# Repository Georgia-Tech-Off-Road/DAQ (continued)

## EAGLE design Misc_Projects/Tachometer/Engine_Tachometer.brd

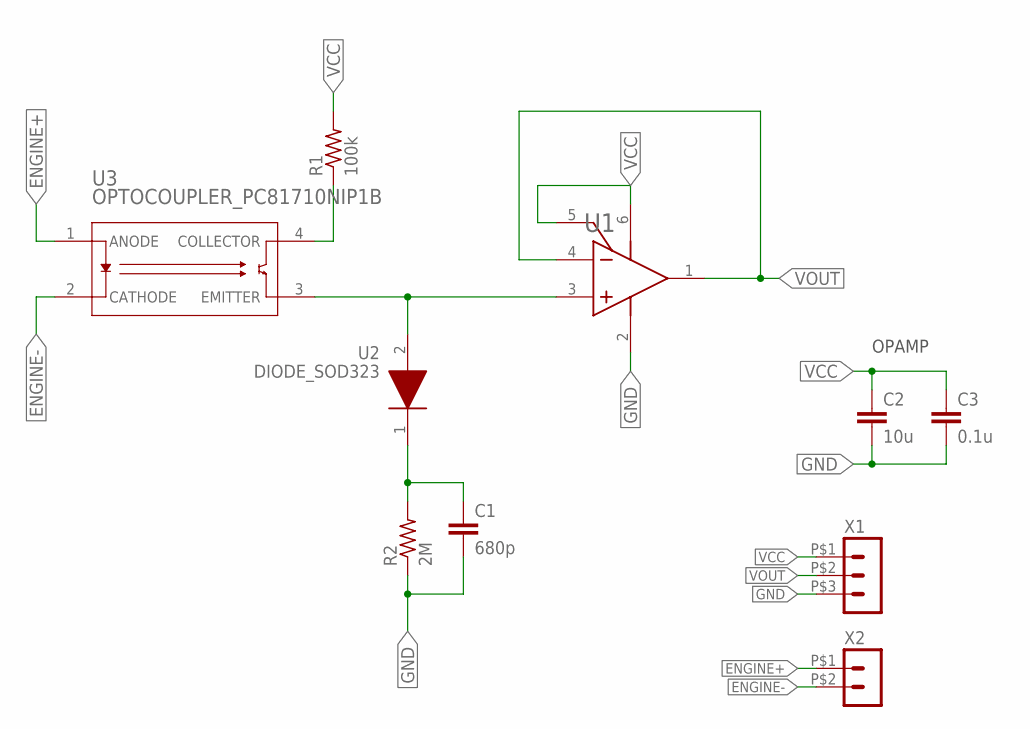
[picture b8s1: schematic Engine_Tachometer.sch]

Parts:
C1: 680p; C0603
C2: 10u; C1206
C3: 0.1u; C0603
R1: 100k; R1206
R2: 2M; R0603
U1: OPAMP_LMH6611MKE; MK06A
U2: DIODE_SOD323; SOD-323_1P8X1P35_ONS
U3: OPTOCOUPLER_PC81710NIP1B; SOP_PC8171_SCT
X1: HEADER_POS3_43650-0300; 43650-0300
X2: HEADER_POS2_43650-0200; 43650-0200

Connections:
ENGINE+: U3.1 (ANODE), X2.P$1 (1)
ENGINE-: U3.2 (CATHODE), X2.P$2 (2)
GND: C1.2, C2.2, C3.2, R2.1, U1.2 (V-), X1.P$3 (3)
unnamed: R1.1, U3.4 (COLLECTOR)
unnamed: U1.3 (IN+), U2.2, U3.3 (EMITTER)
unnamed: C1.1, R2.2, U2.1
VCC: C2.1, C3.1, R1.2, U1.5 (~DIS), U1.6 (V+), X1.P$1 (1)
VOUT: U1.1 (OUT), U1.4 (IN-), X1.P$2 (2)

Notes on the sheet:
OPAMP

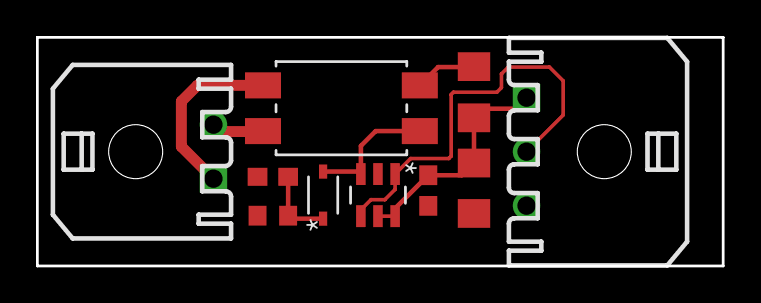
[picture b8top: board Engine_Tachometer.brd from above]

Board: 2 copper layers, 38.1 x 12.7 mm, 10 parts (0 on the bottom side), 8 nets.

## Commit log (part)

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2020-12-27 Testing if I can push to remote
2020-12-31 IMU330DHCX Final Code
2020-12-31 IMU330DHCX Header Upload
2021-01-03 Added the HE sensor case for Rev2
2021-01-14 Add ISM330DHCX Library
2021-01-15 Conceptual Brainstorming Changes
2021-01-15 Added diff library for eagle
2021-01-15 Added relevant mailing lists for recruitment emails.
2021-01-15 Updated .gitignore and cleaned up Eagle autosaves
2021-01-15 Removed Eagle Libraries
2021-01-16 Created HESensorRev3 case and added documentation
2021-01-16 Added STL Files for Printing
2021-01-16 Created file for IMU
2021-01-16 Increase ranges for accel, gyro, and data rates
2021-01-16 Documentation changes
2021-01-17 Eagle files for PCB
2021-01-18 Added schematic and board files
2021-01-20 Updated Eagle board and software
    Added female headers, routed HE inputs
    Added theoretical diff controller code basis
2021-01-23 Made minor edits to documentation
2021-01-23 Added step in eagle libraries guide
2021-01-27 Test example
2021-01-31 Added small functions to utility
2021-01-31 Changed Lib .readme
2021-01-31 Added automatic Arduino library symlinks generator
2021-02-01 Resized speed sensor case for larger shaft
2021-02-03 Fixed parts so that they can actually be assembled.
2021-02-05 Added STL Files for IMU Case Printing
2021-02-09 Renamed folder from "new_project" to "Dyno Board"
2021-02-10 Renamed folder and added Load Cell Manual.
2021-02-13 Fixed data being deleted after stopped collecting bug
2021-02-13 Added changes that I do not remember
2021-02-18 Created documentation for the engine dyno
2021-02-19 Added documentation for engine dyno
2021-02-19 Added lots of changes for first working prototype
2021-02-24 replaced old motor driver; added local libraries
2021-02-24 Minor bug fixes
2021-02-28 pcb from 02-28
2021-03-04 edited h-bridge
2021-03-04 Minor changes on PCB, ready for manufacturing
2021-03-07 Began work on UARTComms class and Sensor class
2021-03-07 small changes to Sensor
2021-03-07 added changes to update function
2021-03-07 Adding __init__ for EngineDyno Layout
2021-03-10 Pseudocoded rest of Comms functions to be written
2021-03-12 Reconstructed FreqMeasureMulti without using FreqMeasureMulti library
2021-03-12 Moved IMU Lib folder code to Libraries folder
2021-03-12 Moved Dyno code in Lib folder to Libraries folder
2021-03-16 Added functionality for zero rpm
2021-03-17 Finished Aux Daq Case
2021-03-19 Seven Segment Code done
2021-03-20 added matlab file for theoretical speed sensor calculations
2021-03-21 Added update for serial input
2021-03-21 Auto stash before merge of "differential_controller" and "origin/differential_controller"
2021-03-21 Fixed compilation errors and implemented switch/serial control mode
2021-03-24 Finished theoretical implementation using FreqMeasureMulti
2021-03-25 Adding data parser for recording and graphing data collected from sensors
2021-03-26 Adding the data parser to change bin data files in to usable data to graph and add to an excel sheet
2021-03-26 Reversed motor pins to work with new differential
2021-03-26 Working UARTComms and SDWrite libraries. Next step is extending Sensor functionality.
2021-03-26 temporary commit
2021-03-26 Tidying the parser and preparing for plotting
2021-03-26 Sensor updates, LDS example
2021-03-27 Fixed some problems with LDS example, Sensor id bug still exists---id needs to be 1 byte for now
2021-03-27 aux daq unit code with two sensors
2021-03-27 Quick fix for diff controller breaking when moving to state 1 and state2
2021-03-27 Added more sensor libraries
2021-03-27 Give to Akash code
2021-03-28 Changes from grind day
2021-03-30 Beginning data parser optimizations
2021-04-01 Need to change branches
2021-04-01 Small changes to DataCollection
2021-04-02 Adding more cleanup to parser
2021-04-02 Added functions to implement for data import
2021-04-02 Added Sensor ID's to Daata
2021-04-04 Before merge with aux_daq_util
2021-04-04 Adding most Import functionality and updating Data and SensorId accordingly
2021-04-04 Added Pinout image and modified Dyno_test to follow pinout
2021-04-06 Renamed Folder to Engine_Dyno
2021-04-06 Updated HEtest.ino to work with new HE Sensor library
2021-04-06 Added psedu-code/code for speed sensor?
    Please double-check
2021-04-07 Finished minimum worked version of SpeedSensor
2021-04-07 Added SpeedSensor to Sensor.h
2021-04-07 Cleaning up parser, adding csv file for data, and beginning update to Sensor objects and ID's
2021-04-07 Updating Sensor ID numbers
2021-04-07 hotfix
2021-04-07 Code ready for dyno test
2021-04-09 Added SerialTest.ino
2021-04-09 Git witchcraft merge
2021-04-10 Comments added
2021-04-11 Code uploaded for the 4/11/2021 test day
    Syntax errors fixed
2021-04-13 Code uploaded for test day 4/11/21
2021-04-17 Fixed errors with Sensor Class
2021-04-17 Adding data parsers
2021-04-17 Updated SensorId
2021-04-17 Changes to mock wireless testing
2021-04-17 Manual merge of dashboard into master
2021-04-21 Adding syntax fixes in import
2021-04-21 Changing serial port to None to get it working
2021-04-23 On the verge of glory
2021-04-25 pls no conflict
2021-04-28 Made better averaging algorithm for speed sensor
2021-05-01 Updated Dashboard Code (non-working)
2021-05-01 Display diff position on dashboard
2021-05-01 Added StateSensor and diff_state functionality for writing diff_state to h_seg on dash
2021-05-12 Updated documentation template
2021-06-02 DashHub code changes from Arizona
2021-06-18 Removed Documentation
2021-06-18 Removed Resources Folder
2021-06-26 Removed HallEffectSpeedSensor
2021-06-29 Removed Libraries
2021-07-08 Updates to First Dyno test
2021-08-21 Added ability to zero load cell
2021-09-03 Created new branch and folder for new 2022 aux_daq
2021-09-06 Added rough draft of shockdyno arduino code
2021-09-12 Added optional headers for strain gauge breakout
2021-09-12 added project for shock dyno
2021-09-19 Working on board files
2021-09-19 Minor DRC fixes and trace thickening
2021-09-19 Minor silkscreen changes
2021-09-19 completed shock dyno PCB schematic
2021-09-20 Boards designs before 9/19 design review
2021-09-22 Moved phat connector
2021-09-24 shock dyno PCB updates
2021-09-26 Just a bit of work I did on Tuesday
2021-09-26 Added kill motor scenario and fixed scale for motor_control
2021-09-26 added name to shock dyno PCB
2021-09-27 More work done to dash hub and dial, gps board added
2021-09-27 Adding design draft of comms testing board
2021-09-28 Finished everything except silkscreen
2021-09-29 final touches to shock dyno PCB
2021-09-29 Adding finished comms testing board
2021-09-29 Updated silkscreen
2021-09-29 final touches to shock dyno PCB part 3
2021-10-01 Linear Regulator
2021-10-06 Added wireless receiver PCB
2021-10-08 Added new linear regulator and XBee silkscreen to dashhub
2021-10-10 Added gps to dashhub
2021-10-15 Added OLED
2021-10-17 Added missing capacitor values
2021-10-17 Moving stuff around on the dashhub #pain
2021-10-19 Changed names on dashboard to reflect pins
2021-10-20 Changed regulator placement
2021-10-22 Fixed the dashhub #everything
2021-10-27 Added resistor values to dashhub and board
2021-10-31 Fixed IMU test code
2021-11-04 IMU Code works with aux_daq
2021-11-05 OLED code added
2021-11-05 Added OLED code
2021-11-05 Added Aux Daq Code and wireless comms throughput
2021-11-12 Test day AuxDaq code
2021-12-07 Added Testing Day Nov 20 Code
    It doesn't work
2021-12-07 Finished routing aux daq
2021-12-13 Started making Aux Daq V2 Case
2021-12-29 Did Aux Daq Design Review
2022-01-14 oriented load cell connector correctly
2022-01-14 added labels to silkscreen on shock dyno PCB
2022-01-14 Edited Dashboard code
2022-01-19 Updated Aux Daq PCB to include LED and button outputs
2022-01-21 Added aux daq definitions file
2022-01-24 Finished shock dyno updates
2022-02-02 Removed incorrect IMU case
2022-02-06 Updated all dashboard stuff
2022-02-11 Dashboard Code Organization
2022-02-13 modified Shock_Dyno.ino for ads8688
2022-02-20 fixed Shock Dyno disable
2022-02-28 removed relay from shock dyno
2022-03-02 Removed bad dashboard code
2022-03-04 changed strain gauge board connectors to microfit
2022-03-04 Added new Light Gate boards
2022-03-06 Light Gate Updates
2022-03-06 Fixeed light gate start board
2022-03-07 Created second aux daq digital breakout
2022-03-09 Coded light gates
2022-03-13 Attached GPS block for dashboard
2022-04-01 Updated Wireless Receiver Code
2022-04-03 Updated DynoTest Code
2022-04-07 COde from testing day
2022-04-10 Updated aux daq case design and added demo code for end of year review
2022-04-24 added power trace to shock dyno board ADC
2022-04-24 added more clearance for standoff pins on shock dyno
2022-04-24 edit dashboard code
2022-05-06 Wrote CVTStiffness testing code
2022-05-06 FIXED DASHBOARD LETS GOOO
2022-06-02 Dashboard code from Tennessee
2022-08-25 Engine dyno speed sensor updates
2022-09-13 new pcb files
2022-09-28 Updated to 7mil trace instead of 5mil
2022-10-02 Working on dashboard code
2022-10-09 CODE
2022-10-30 Updated pull ups on dashboard
2022-11-03 Wireless Communications Consolidation
2022-11-18 change file name
2022-11-30 Battery box and commsboardv2 update
2022-12-02 Updated for better dimensions
2023-01-13 Updated dashboard speed formulas and added some documentation comments
2023-01-15 GPS test code started
2023-01-16 Updated dashboard mps names for c++ conflict
2023-01-20 Created PCB For Driver Comms Board + Misc.
    Edited sketch for driver comms test board and then designed corresponding PCB. Pushed some changes with schock dyno and imu test code that are minor (and I don't remember making).
2023-01-20 Updated dash hub to power GPS with 5V
2023-01-25 Battery Box Update v4
    Changed sides of radio antenna hole and wires hole.
2023-01-27 Finalized PCB and started code
2023-02-01 Fully Updated Code to send to Driver
2023-02-03 Created code for receiving messages on dashboard board
2023-02-05 Finalized dashboard code to receive and display messages to driver
2023-02-17 Changes so only sends when a different message is sent
2023-02-26 Testing ADC's on auxdaq, made test ino file and copied board files from last year to edit them
2023-03-03 Updating Code for Testing Driver Comms
2023-03-03 Tested and Finalized Receiver Code
2023-03-08 Comms Test Board update
    changed some stuff
2023-03-08 CVT Temp Sensor PCB
    Version 1.0
2023-03-08 Added connector to IMU board
2023-03-10 Finished IMU board
2023-03-10 not sure what this is
2023-04-16 Updated Sender Board
    Corrected orientation of Xbee and also power supply.
2023-04-17 Updated dashboard code to use onboard indication LEDS
    This is different from driver comms board indication
2023-04-21 Updated Driver Message Board so that LEDs work
2023-04-29 auxDaq code used for testing days in April
2023-04-29 code that maybe interfaces sdWrite button from daata to auxDaq
2023-05-04 Updated dashboard with gps
2023-05-05 Teensy to teensy comms maybe
2023-05-06 Fix block ids
2023-05-06 Bug fix
2023-05-07 print gps
2023-08-25 same as below commit
2023-08-30 imudash wip
2023-09-01 Add dashboard IMU to comms path
2023-09-09 Switch speed sensors
2023-09-17 Unneeded
2023-09-24 Fix force sensor maybe
2023-10-01 test
    random test push to fix vishnav's git set up
2023-10-01 Revert "test"
    This reverts commit ca83d801667cfc2b1897a25c9061b99a7f00245b.
2024-04-04 changed pin assignments and commented out dashboard signals
2024-04-14 LEDS
2024-04-16 changed port numbers, fixed constructor
2024-04-21 Changes On Ohio 2023 to add LEDs
